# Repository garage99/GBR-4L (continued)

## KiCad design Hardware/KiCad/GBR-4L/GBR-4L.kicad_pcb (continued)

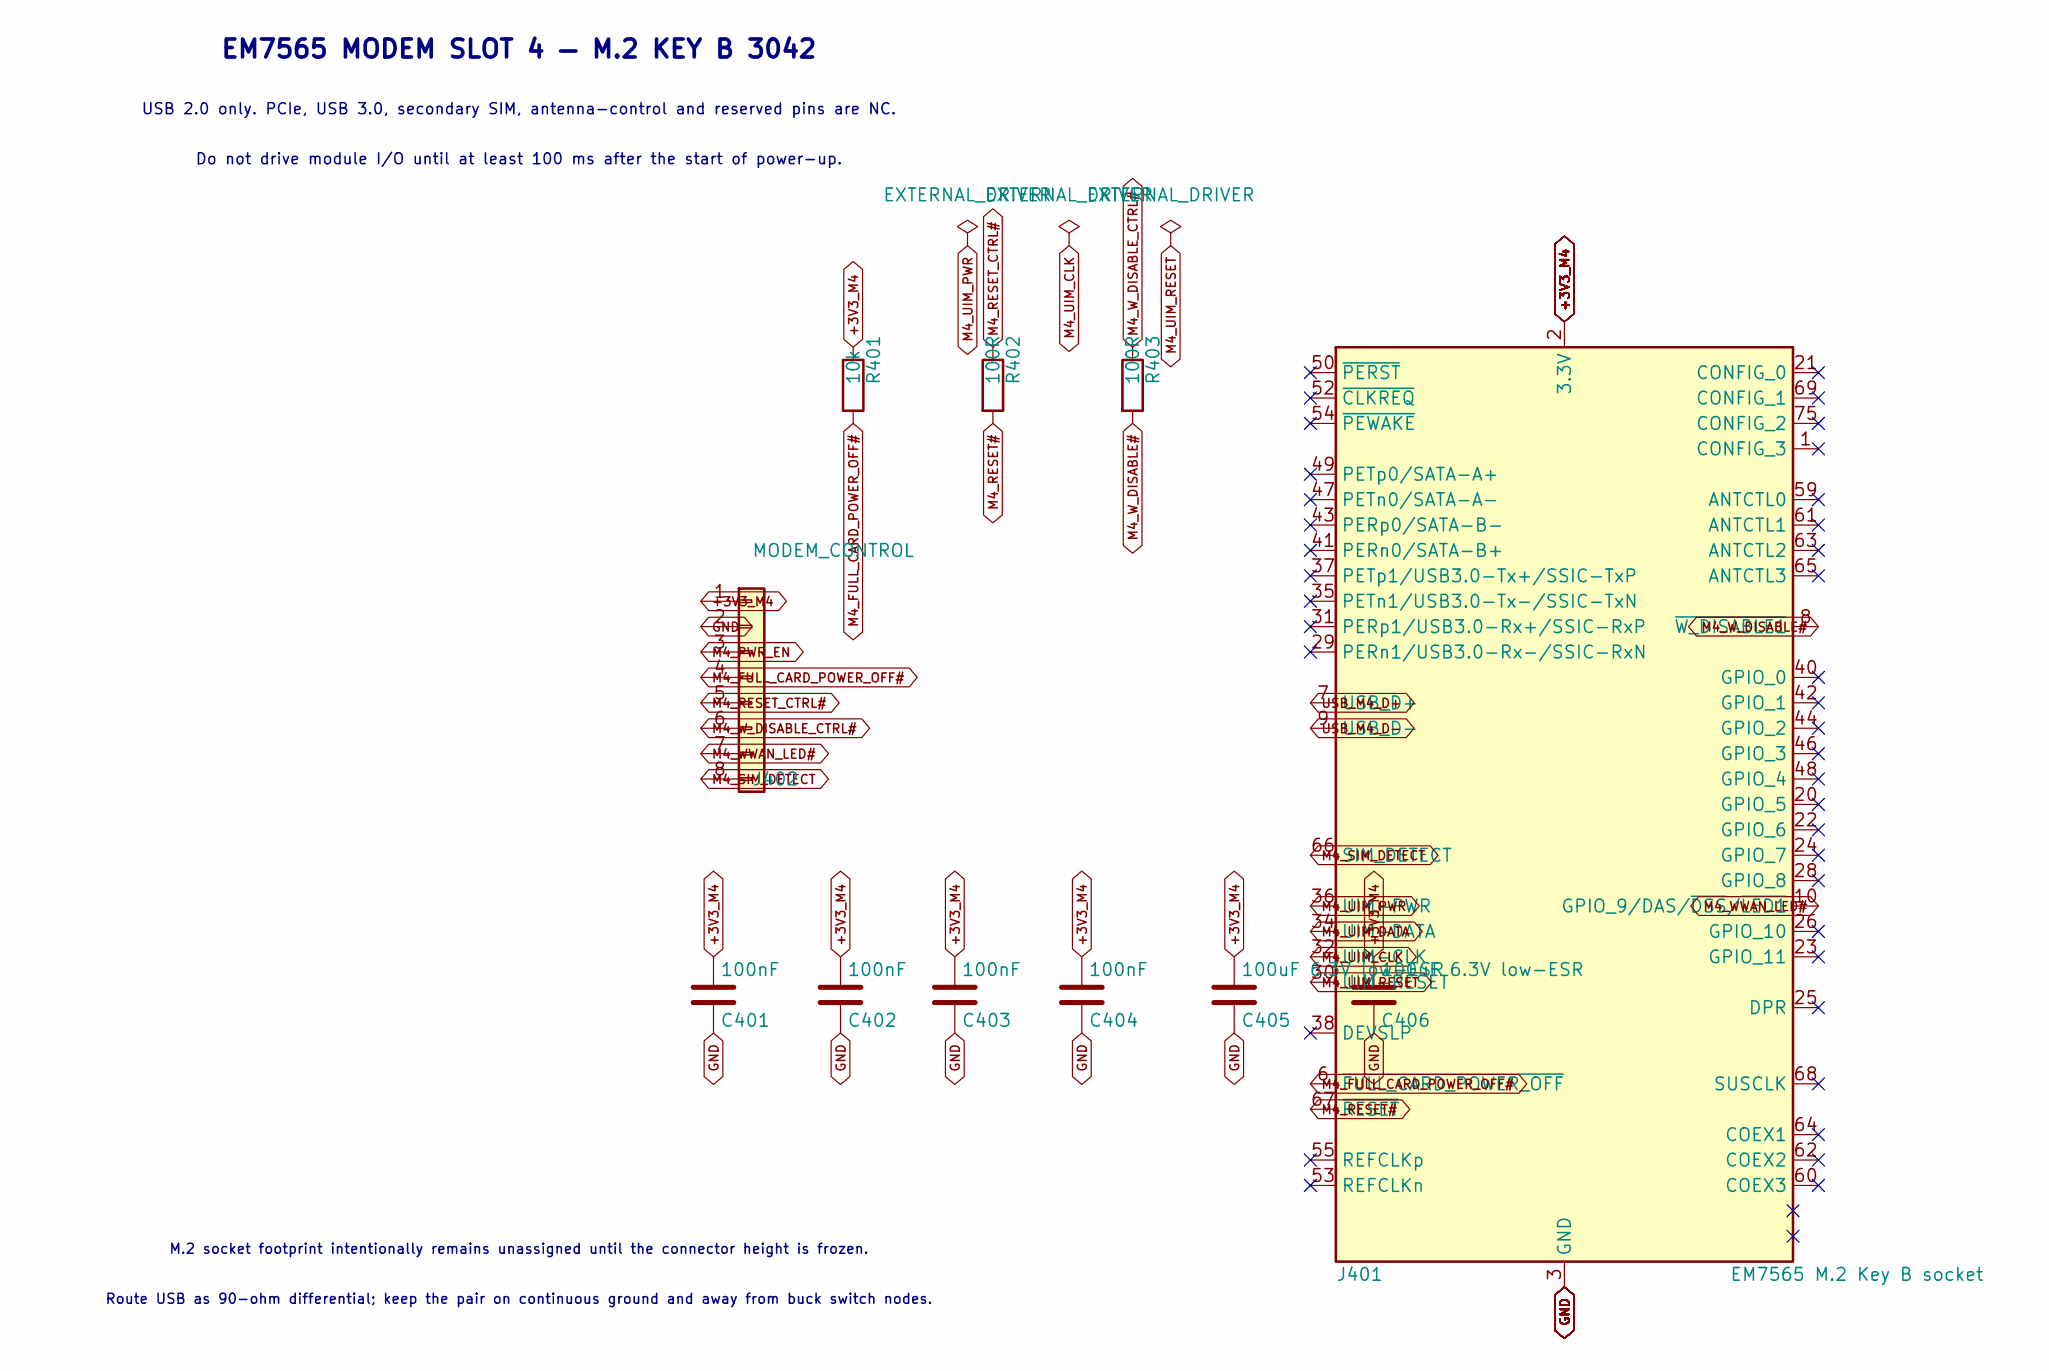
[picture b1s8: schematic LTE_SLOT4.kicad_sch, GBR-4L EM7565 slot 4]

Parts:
C401, C402, C403, C404: 100nF; C_0603_1608Metric
C405, C406: 100uF 6.3V low-ESR; C_1210_3225Metric
J401: EM7565 M.2 Key B socket
J402: MODEM_CONTROL; PinHeader_1x08_P2.54mm_Vertical
R401: 10k; R_0603_1608Metric
R402, R403: 100R; R_0603_1608Metric

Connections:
+3V3_M4: C401.1, C402.1, C403.1, C404.1, C405.1, C406.1, J401.2 (3.3V), J401.4 (3.3V), J401.70 (3.3V), J401.72 (3.3V), J401.74 (3.3V), J402.1, R401.1; also elsewhere on the board
GND: C401.2, C402.2, C403.2, C404.2, C405.2, C406.2, J401.3 (GND), J401.5 (GND), J401.11 (GND), J401.27 (GND), J401.33 (GND), J401.39 (GND), J401.45 (GND), J401.51 (GND), J401.57 (GND), J401.71 (GND), J401.73 (GND), J402.2; also elsewhere on the board
M4_FULL_CARD_POWER_OFF#: J401.6 (~FULL_CARD_POWER_OFF), J402.4, R401.2
M4_PWR_EN: J402.3; also elsewhere on the board
M4_RESET#: J401.67 (~RESET), R402.2
M4_RESET_CTRL#: J402.5, R402.1; also elsewhere on the board
M4_SIM_DETECT: J401.66 (SIM_DETECT), J402.8; also elsewhere on the board
M4_UIM_CLK: J401.32 (UIM-CLK); also elsewhere on the board
M4_UIM_DATA: J401.34 (UIM-DATA); also elsewhere on the board
M4_UIM_PWR: J401.36 (UIM-PWR); also elsewhere on the board
M4_UIM_RESET: J401.30 (UIM-RESET); also elsewhere on the board
M4_WWAN_LED#: J401.10 (GPIO_9/DAS/~DSS/~LED1), J402.7; also elsewhere on the board
M4_W_DISABLE#: J401.8 (~W_DISABLE1), R403.2
M4_W_DISABLE_CTRL#: J402.6, R403.1; also elsewhere on the board
USB_M4_D+: J401.7 (USB_D+); also elsewhere on the board
USB_M4_D-: J401.9 (USB_D-); also elsewhere on the board

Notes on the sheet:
EM7565 MODEM SLOT 4 — M.2 KEY B 3042
USB 2.0 only. PCIe, USB 3.0, secondary SIM, antenna-control and reserved pins are NC.
Route USB as 90-ohm differential; keep the pair on continuous ground and away from buck switch nodes.
M.2 socket footprint intentionally remains unassigned until the connector height is frozen.
Do not drive module I/O until at least 100 ms after the start of power-up.

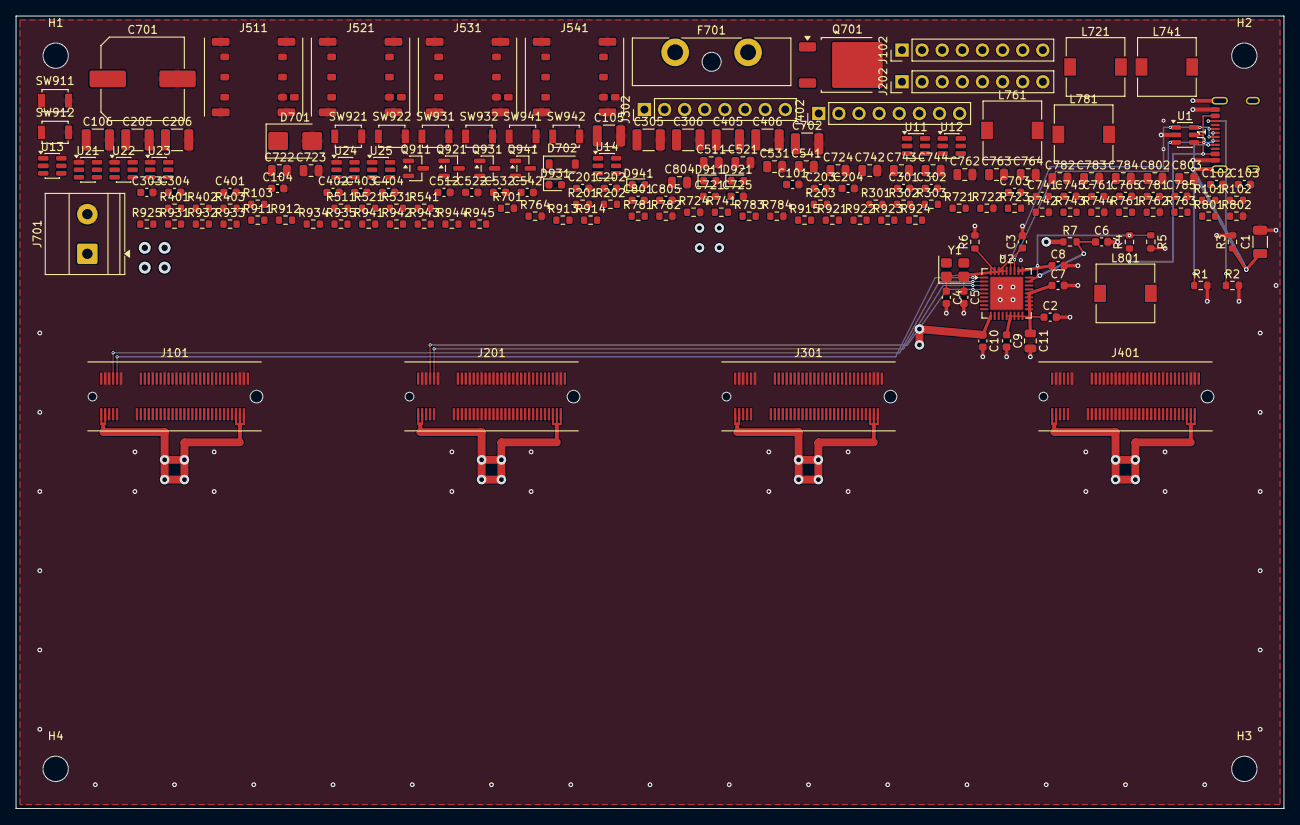
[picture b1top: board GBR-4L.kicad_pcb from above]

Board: 4 copper layers, 160.0 x 100.0 mm, 188 parts (0 on the bottom side), 108 nets.

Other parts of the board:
H1, H2, H3, H4: M3; MountingHole_3.2mm_M3
U11, U12, U13, U14: LOW-CAP SIM ESD ARRAY; SOT-23-6

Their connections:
GND: U11.2 (GND), U12.2 (GND), U13.2 (GND), U14.2 (GND); also elsewhere on the board
M1_SIM_DETECT: U11.6 (IO5); also elsewhere on the board
M1_UIM_CLK: U11.4 (IO3); also elsewhere on the board
M1_UIM_DATA: U11.5 (IO4); also elsewhere on the board
M1_UIM_PWR: U11.1 (IO1); also elsewhere on the board
M1_UIM_RESET: U11.3 (IO2); also elsewhere on the board
M2_SIM_DETECT: U12.6 (IO5); also elsewhere on the board
M2_UIM_CLK: U12.4 (IO3); also elsewhere on the board
M2_UIM_DATA: U12.5 (IO4); also elsewhere on the board
M2_UIM_PWR: U12.1 (IO1); also elsewhere on the board
M2_UIM_RESET: U12.3 (IO2); also elsewhere on the board
M3_SIM_DETECT: U13.6 (IO5); also elsewhere on the board
M3_UIM_CLK: U13.4 (IO3); also elsewhere on the board
M3_UIM_DATA: U13.5 (IO4); also elsewhere on the board
M3_UIM_PWR: U13.1 (IO1); also elsewhere on the board
M3_UIM_RESET: U13.3 (IO2); also elsewhere on the board
M4_SIM_DETECT: U14.6 (IO5); also elsewhere on the board
M4_UIM_CLK: U14.4 (IO3); also elsewhere on the board
M4_UIM_DATA: U14.5 (IO4); also elsewhere on the board
M4_UIM_PWR: U14.1 (IO1); also elsewhere on the board
M4_UIM_RESET: U14.3 (IO2); also elsewhere on the board
